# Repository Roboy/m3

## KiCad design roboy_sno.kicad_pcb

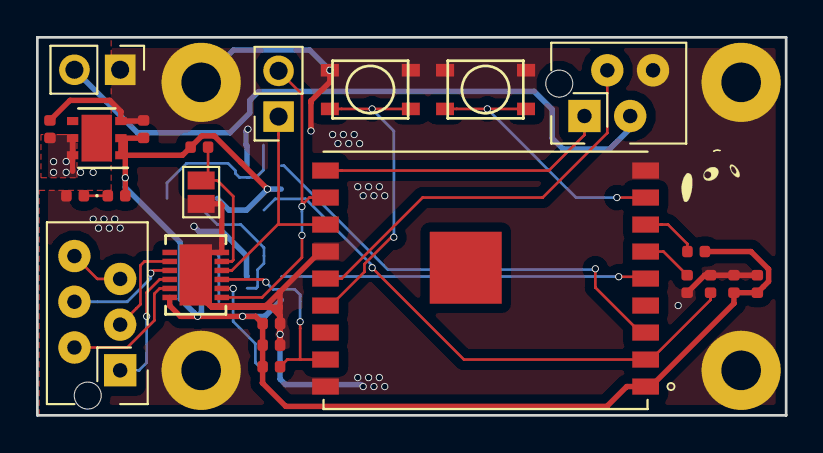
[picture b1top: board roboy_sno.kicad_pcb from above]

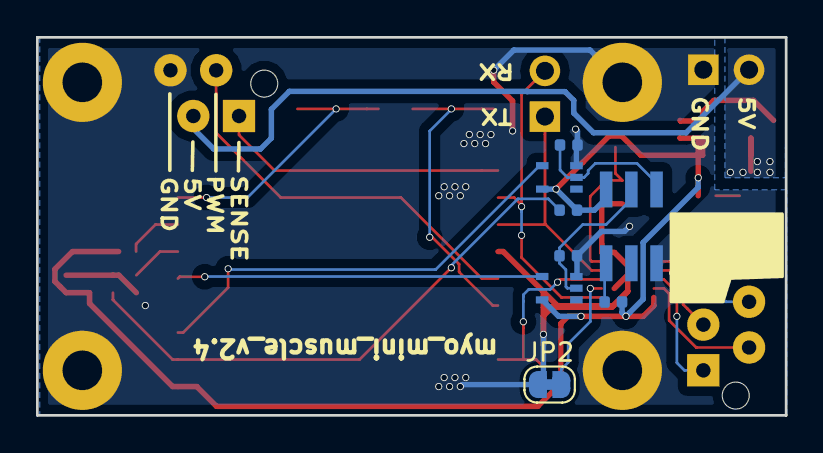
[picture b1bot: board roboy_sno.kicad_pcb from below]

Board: 2 copper layers, 41.6 x 21.0 mm, 38 parts (8 on the bottom side), 26 nets.

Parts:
C1, C2, C3, C5: 0.1uF; C_0402_1005Metric
C4, C6, C7: 10uF; C_0402_1005Metric
D1: LED; LED_0402_1005Metric
H1, H2, H6, H7: MountingHole; MountingHole_2.2mm_M2_Pad
H3: LABEL; R1_ear_silk_5.5mm
H4: LABEL; R1_eyes_mask_5.5mm
H5: LABEL; R1_face_mask_5.5mm
J1, J2: SCHMITT_TRIGGER; SC70-5
J3: UART; PinSocket_1x02_P2.54mm_Vertical
J4: power; PinHeader_1x02_P2.54mm_Vertical
J5: Conn_01x04_Male; TE-Connectivity_Micro-Match_connector_02x02_Pitch_1.27mm
J6: tcut1350; tcut1350x01
J7: ICEBUS; TE-Connectivity_Micro-Match_connector_02x03_Pitch_1.27mm
JP1: SolderJumper_2_Open; SolderJumper-2_P1.3mm_Open_Pad1.0x1.5mm
JP2: SolderJumper_2_Bridged; SolderJumper-2_P1.3mm_Bridged_RoundedPad1.0x1.5mm
R1, R2, R3, R4, R8, R9: 10k; R_0402_1005Metric
R5, R6: 2k; R_0402_1005Metric
R7: 47; R_0402_1005Metric
SW1: RESET; PTS815-SJK
SW2: BOOT; PTS815-SJK
U1: LTC2855CDEPBF; ltc2855
U2: ESP-WROOM-02U; MODULE_ESP-WROOM-02U
U3: LD39200; DFN-6-1EP_3x3mm_P0.95mm_EP1.7x2.6mm

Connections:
+3V3: C2.1, C3.1, C4.2, C5.1, C6.2, D1.2, J1.5, J2.5, J6.3, R1.1, R2.2, R3.2, R7.1, R9.2, U1.12, U2.1, U3.1, U3.2
+5V: C7.2, J4.2, J5.3, U3.5, U3.6
/h_Rx: J7.2, U1.11
/h_Tx: J7.4, U1.9
/l_Rx: J7.1, U1.10
/l_Tx: J7.3, U1.8
/term_te: JP1.1, R2.1, U1.5
DE: R9.1, U1.3, U2.17
E0: J1.2, J6.1, R5.1
E0_filtered: J1.4, U2.3
E1: J2.2, J6.2, R6.2
E1_filtered: J2.4, U2.5
GND: C1.1, C2.2, C3.2, C4.1, C5.2, C6.1, C7.1, H1.1, H2.1, H6.1, H7.1, J1.3, J2.3, J4.1, J5.4, J6.6, JP1.2, JP2.1, R4.2, R5.2, R6.1, R8.1, SW1.1, SW2.1, U1.6, U1.13, U2.9, U2.13, U2.18, U3.3
MOTOR: J5.2, U2.14
MOTOR_SENSE: J5.1, U2.10
unnamed: C1.2, R3.1, U2.2
unnamed: D1.1, R8.2
unnamed: J6.4, R7.2
unnamed: JP2.2, U1.2
unnamed: R1.2, U2.7
unnamed: R4.1, U2.6
unnamed: SW1.2, U2.15
unnamed: SW2.2, U2.8
RXD: J3.2, U1.1, U2.11
SHIELD: J7.5, J7.6
TXD: J3.1, U1.4, U2.12

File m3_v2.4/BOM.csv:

Id,Designator,Package,Quantity,Price per unit,Designation,Supplier and ref
2,"U2,U2,U2,U2,U2,U2,U2,U2",MODULE_ESP-WROOM-02U,8,2.88 €,ESP-WROOM-02U,https://www.mouser.de/ProductDetail/Espressif-Systems/ESP-WR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
3,"C1,C1,C1,C1,C1,C1,C1,C2,C2,C2,C2,C2,C2,C2,C3,C3,C3,C3,C3,C3,C3,C5,C5,C5,C5,C5,C5,C5,C1,C2,C3,C5",C_0402_1005Metric,32,0.01 €,0.1uF,
4,"R5,R5,R5,R5,R5,R5,R5,R6,R6,R6,R6,R6,R6,R6,R5,R6",R_0402_1005Metric,16,0.01 €,2k,
5,"R3,R3,R3,R3,R3,R3,R3,R9,R9,R9,R9,R9,R9,R9,R8,R8,R8,R8,R8,R8,R8,R2,R2,R2,R2,R2,R2,R2,R1,R1,R1,R1,R1,R1,R1,R4,R4,R4,R4,R4,R4,R4,R1,R2,R3,R4,R8,R9",R_0402_1005Metric,48,0.01 €,10k,
9,"U3,U3,U3,U3,U3,U3,U3,U3",DFN-6-1EP_3x3mm_P0.95mm_EP1.7x2.6mm,8,0.77 €,LD39200,https://www.mouser.de/ProductDetail/STMicroelectronics/LD392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
10,"U1,U1,U1,U1,U1,U1,U1,U1",ltc2855,8,2.46 €,LTC2855CDEPBF,https://www.mouser.de/ProductDetail/Analog-Devices-Linear-Te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
12,"J1,J1,J1,J1,J1,J1,J1,J2,J2,J2,J2,J2,J2,J2,J1,J2",SC70-5,16,0.16 €,SCHMITT_TRIGGER,https://www.mouser.de/ProductDetail/595-SN74LVC1G17DCKR
16,"C7,C7,C7,C7,C7,C7,C7,C6,C6,C6,C6,C6,C6,C6,C4,C4,C4,C4,C4,C4,C4,C4,C6,C7",C_0402_1005Metric,24,0.01 €,10uF,
17,"R7,R7,R7,R7,R7,R7,R7,R7",R_0402_1005Metric,8,0.01 €,47,
20,"SW1,SW1,SW1,SW1,SW1,SW1,SW1,SW1,SW2,SW2,SW2,SW2,SW2,SW2,SW2,SW2",PTS815-SJK,16,0.15 €,RESET,https://www.mouser.de/ProductDetail/CK/PTS815-SJK-250-SMTR-L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
21,"J6,J6,J6,J6,J6,J6,J6,J6",tcut1350x01,8,1.06 €,tcut1350,https://www.mouser.de/ProductDetail/Vishay-Semiconductors/TC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
22,"D1,D1,D1,D1,D1,D1,D1,D1",LED_0402_1005Metric,8,0.22 €,LED,https://www.mouser.de/ProductDetail/Wurth-Elektronik/150040V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
,,,total no parts:,total price:,,
,,,200,63.70 €,,

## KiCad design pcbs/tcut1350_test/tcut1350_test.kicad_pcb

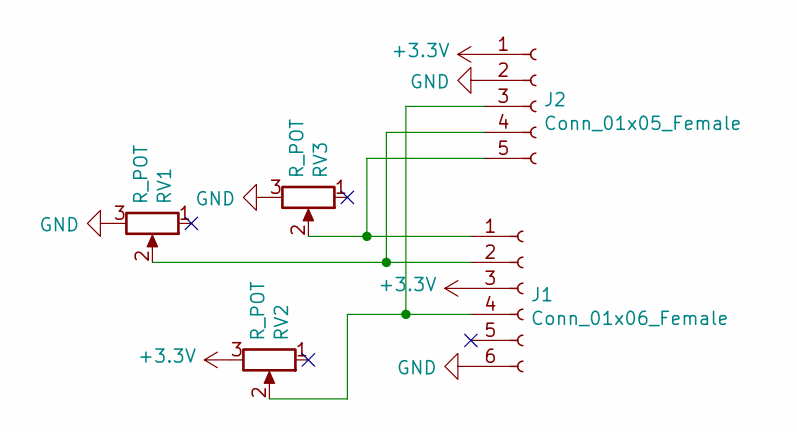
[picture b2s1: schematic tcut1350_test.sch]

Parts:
J1: Conn_01x06_Female; tcut1350x01
J2: Conn_01x05_Female; PinSocket_1x05_P2.54mm_Vertical
RV1, RV2, RV3: R_POT; Potentiometer_Bourns_PTA2043_Single_Slide

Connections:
+3V3: J1.3, J2.1, RV2.3
GND: J1.6, J2.2, RV1.3, RV3.3
unnamed: J1.1, J2.5, RV3.2
unnamed: J1.2, J2.4, RV1.2
unnamed: J1.4, J2.3, RV2.2

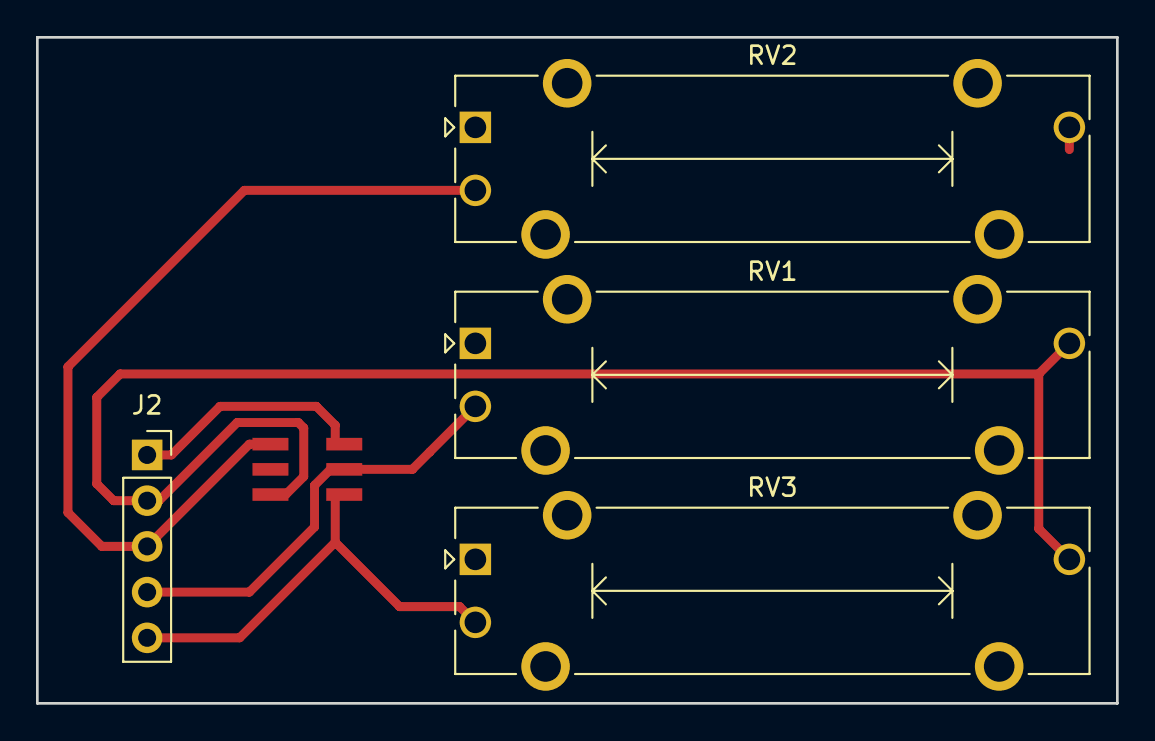
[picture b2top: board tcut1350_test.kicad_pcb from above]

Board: 2 copper layers, 60.0 x 37.0 mm, 5 parts (0 on the bottom side), 5 nets.

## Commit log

2018-12-19 initial
2018-12-20 receiving and sending
2018-12-20 with control modes
2018-12-28 done pcb layout
2018-12-29 with espros
2019-01-02 with ros interface using rosserial over wifi
2019-01-02 with gains depending on the control mode
2019-01-03 with stl export
2019-02-02 esp32-wroom-2d without usb->uart
2019-02-02 esp-wroom32 ready
2019-05-09 with freertos version, servo and angle working already
2019-05-09 with udp biatch
2019-05-09 sending and receiving
2019-05-09 position control working
2019-05-09 with submodules and compiler for esp freertos
2019-05-09 with readme
2019-05-10 with bigger esp32
2019-05-10 with pinout
2019-05-10 new version with esp32 ready and ordered on pcbway
2019-05-12 forgot cmake lists
2019-05-12 updated install
2019-05-12 moved to c++, untested
2019-05-12 with pcb step export
2019-05-12 better motor pins placdement
2019-05-14 pcbway requirements
2019-05-14 with schematics
2019-05-15 with corrected ground plane
2019-05-15 adc draft
2019-05-16 adc draft done
2019-05-16 with all components working
2019-05-17 final pcb order?
2019-05-23 with stepper motor control example
2019-05-27 with real pinout of m3 units
2019-05-27 with all control modes and connection to gui
2019-05-28 with buttons
2019-07-12 with displacement control stabil!
2019-07-16 saver
2019-10-09 we need float gains at least
2019-10-11 release a bit on boot
2019-11-02 with global hard-coded id
2019-11-22 with optical encoder
2019-11-25 with optical encoder step
2019-12-03 make it small
2019-12-11 using optical encoder
2019-12-19 exported
2020-01-02 rev 2.2 ordered on aisler
2020-01-13 with 8266ex version
2020-01-13 with pos control working
2020-01-13 changed pwm and motor sense to io 4/5, because the bloddy io16 cannnot be used as an interrupt pin
2020-01-16 with direct_pwm, integral and better initial gains
2020-01-17 with test circuit for optical encoder
2020-01-21 with optical quadrature
2020-01-30 shitty low-pass filter
2020-01-30 schmitt trigger adapter
2020-02-19 fixed bug in smitt-trigger adapter
2020-03-05 with rs485
2020-03-05 with bom
2020-03-12 bigger panel
2020-03-16 mouse bite bigger distances
2020-03-17 fixed create array
2020-03-23 with icebus
2020-04-13 with icebus mux
2020-05-14 with gain multiplier
2020-06-25 with optical encoder footprint
2020-07-07 with tolerances
2020-09-16 with direct_pwm control mode and gain range closer to iceboard gains
2020-11-11 Changed README.md to be a readme, and added an env-setup file that generates the correct paths relative to its location. Please source env-setup in the future.
2020-11-11 Fixed .gitignore to not exclude the required libraries in the xtensa-lx106-elf toolchain. Hope it works.
2020-11-11 Okay it works now! I'm an idiot forgot the \! in the gitignore >_<
2021-02-03 Fixed angle readout implementation and priorities. Started converting pwm task for servo to proper library. Fixed setpoint being uint32_t, it should be signed.
2021-02-03 PWM and control computation working properly now. Adjusted some initial conditions and enabled full PWM by default (servo isn't too fast). Culprits were some esoteric default casting issues, see comm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
2021-02-04 Included sample period in PID computation everything much smoother now. Implemented derivative of process variable to prevent derivative kick, also derivative exponential average filtering. On the fl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
2021-02-09 Implemented velocity calculation and filtering, and tuned loop parameters. Position data is now filtered, also reduced tolerance for cycle time mismatch (should get more accurate readings). Finally i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
2021-02-09 Added protection when trying to set a displacement with the wrong sign relative to the mirrored setting.
2021-02-10 PWM limit can now be set via icebus. Was set constant during testing.
2021-02-10 Removed spooling reversal protection for displacement mode.
2021-02-14 Updated filter coefficient for position sensor. Now equivalent to averaging roughly 9 samples, w = 2/(k+1).
